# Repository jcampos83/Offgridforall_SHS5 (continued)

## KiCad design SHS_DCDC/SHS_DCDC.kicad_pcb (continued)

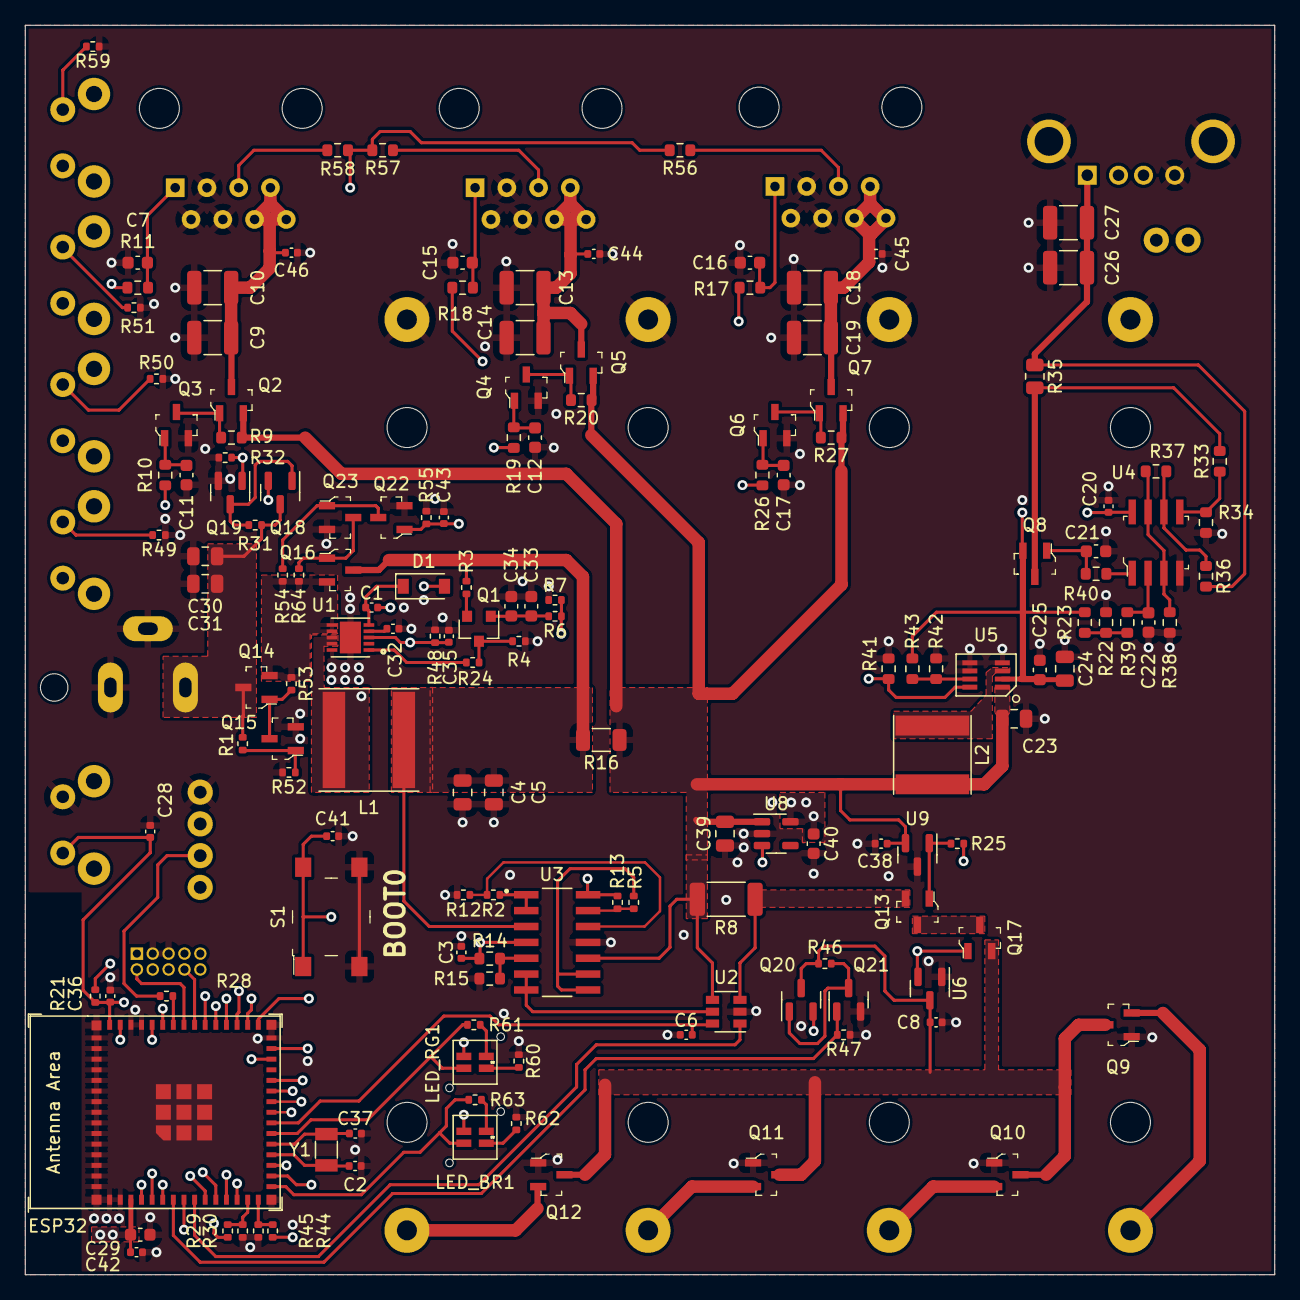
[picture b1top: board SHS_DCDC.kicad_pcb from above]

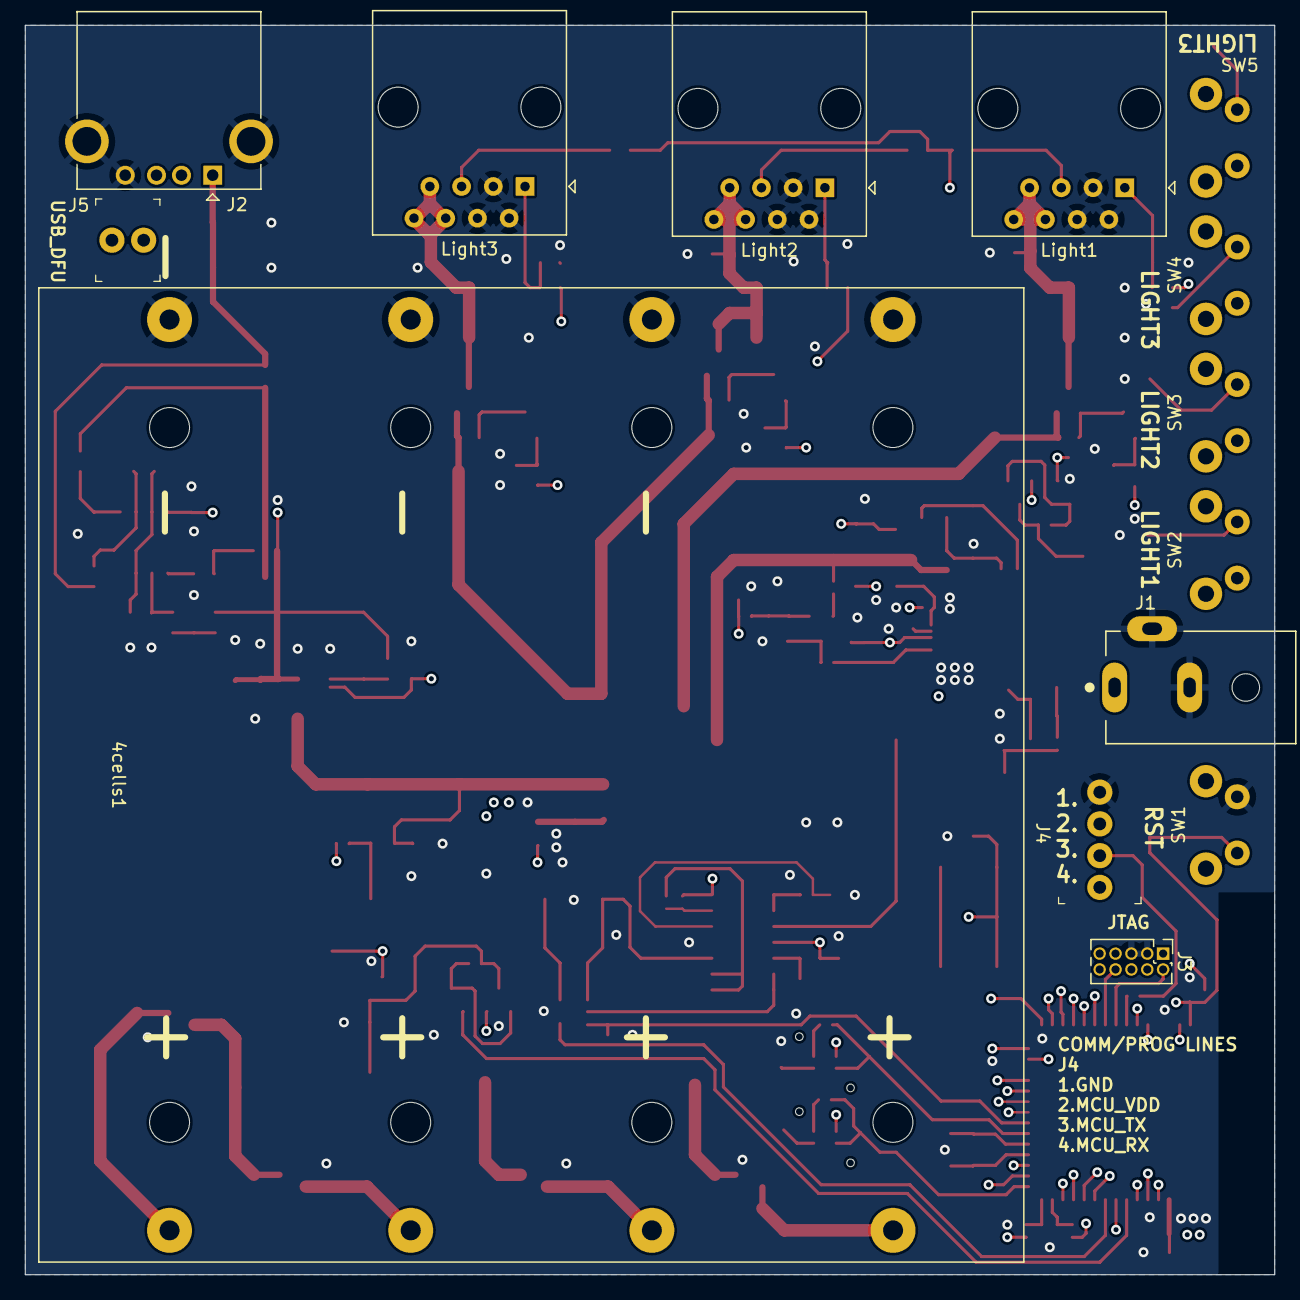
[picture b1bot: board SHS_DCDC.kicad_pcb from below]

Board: 6 copper layers, 100.0 x 100.0 mm, 165 parts (14 on the bottom side), 106 nets.

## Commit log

2021-10-04 testpush
2021-10-31 20213110
2022-05-05 esp32 s2 mini placed
2022-11-20 Commit_GitHubgDesktop
    Try of Github desktop
2023-01-23 Ubuntu transfer
    Commit before transfer onto Ubuntu
2023-02-19 Commit_190223
    Normal commit
2023-02-19 Commit_190223_2
    Commit before checking one older schematic
2023-02-19 Commit_Fix
    Fix to move back to ESP32
2023-03-01 Commit010323
    Progress on the USB current limitation
2023-03-02 Error fix on DCDC block
    Wrong pinout on DCDC block that needed to be fixed
2023-03-13 ProgressMisc
2023-03-14 Bif fix
    Big fix on DCDCOUT and LOAD signal
2023-03-21 OCP
    Adding overcharge protection
2023-03-22 6 layers PCB
    Decision to move to a 6 layers PCB to ease the PCB routing
2023-03-23 PV & BAT V sense
    Adding 2 same blocks allowing the measure by ADC of the PV and Battery voltage on demand through power gating technique
2023-03-27 ADC_PV & BAT
    Blocks related to ADC reading of PV and BAT added on the physical board.
2023-04-17 3D rendering progress
2023-04-24 3D missing part
    Many parts with no 3D view, have completed all of them
2023-05-09 ESP32 cornering
    Moving the ESP32 on the bottom corner of the board
2023-08-12 DFU update
    PCB update to setup 3 ways of FW/Debug capability:
    1. JTAG (FW & Debug)
    2. USB DFU (FW & Debug)
    3. UART (FW only)
    With BOOT0 button installed too
2023-08-13 PV input Power
    Big modification on the PV input power protection, precisely on the reverse battery current protection, and also on the switch between direct PV charging and the DCDC converter
2023-08-13 Light bulb drive update
2023-08-24 Newbutton
    New button whose job is to tell the MCU the user wants to establish a BLE connection with the SHS, in order to configure it.
2023-09-13 LED
    Placement of the 2nd dual LED
2023-09-28 Final_check stage
2023-10-16 Starting DRC
2023-10-17 Commit before reannotation
    Plan to test the reannotation feature.
2023-10-17 Commit update
    Failure of testing the geographical reannotation feature. I have cancelled it myself and now i commit to the normal version.
2023-10-24 Testpoints
    All the tests points have been placed
2023-10-25 Gerber
    Gerber output, ready to send to JLCPCB
